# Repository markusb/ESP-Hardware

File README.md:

<H1>ESP-Hardware</H1>
<p>This repository contains my collection of ESP-Related hardware designs

<h2>ESP-8285 Miniboard</h2>

<p>Small DIL-size board for an ESP8285 Wifi microcontroller
<p>There already are a bunch of ESP boards and modules around, but the either add a full programming circuit or are modules with small pins to solder.
<p>This wants to combine the best of both, with standard 2.54mm pinheaders and easy programming, but on a separate board. So you plug in the programmer when you want to download firmware, but remove it when you don't need it anymore.
<ul>
<li>DIL size, plugs directly into a breadboard
<li>Breaks out all IO pins, not an arbitrary selection like most modules
<li>Antenna and crystal on board, ready to, just add power
<li>Optional red power and blue tx LED, to see whats going on, can be removed to save power
<li>No other, potentially unwanted hardware to get in the way of your design
</ul>

<h2>ESP82xx Programmer</H2>
<p>USB programmer built for the ESP-Miniboard, but it will work for normal ESP82xx circuits and most modules as well.
<p>As the ESP-Miniboard has no programmer, you need it separately. So it goes on this second board, to be removed when no longer in use.
<ul>
<li>USB-Serial chip (CH340)
<li>3.3V Regulator to feed the ESP from USB during programming (no external power needed)
<li>3.3V supply has a jumper to disable power and a polyfuse to protect from a short
<li>Nodemcu reset circuit to decouple the RTS/DTR lines from reset and GPIO0
<li>Works with any ESP module, just connect up the pins and off you go !
</ul>

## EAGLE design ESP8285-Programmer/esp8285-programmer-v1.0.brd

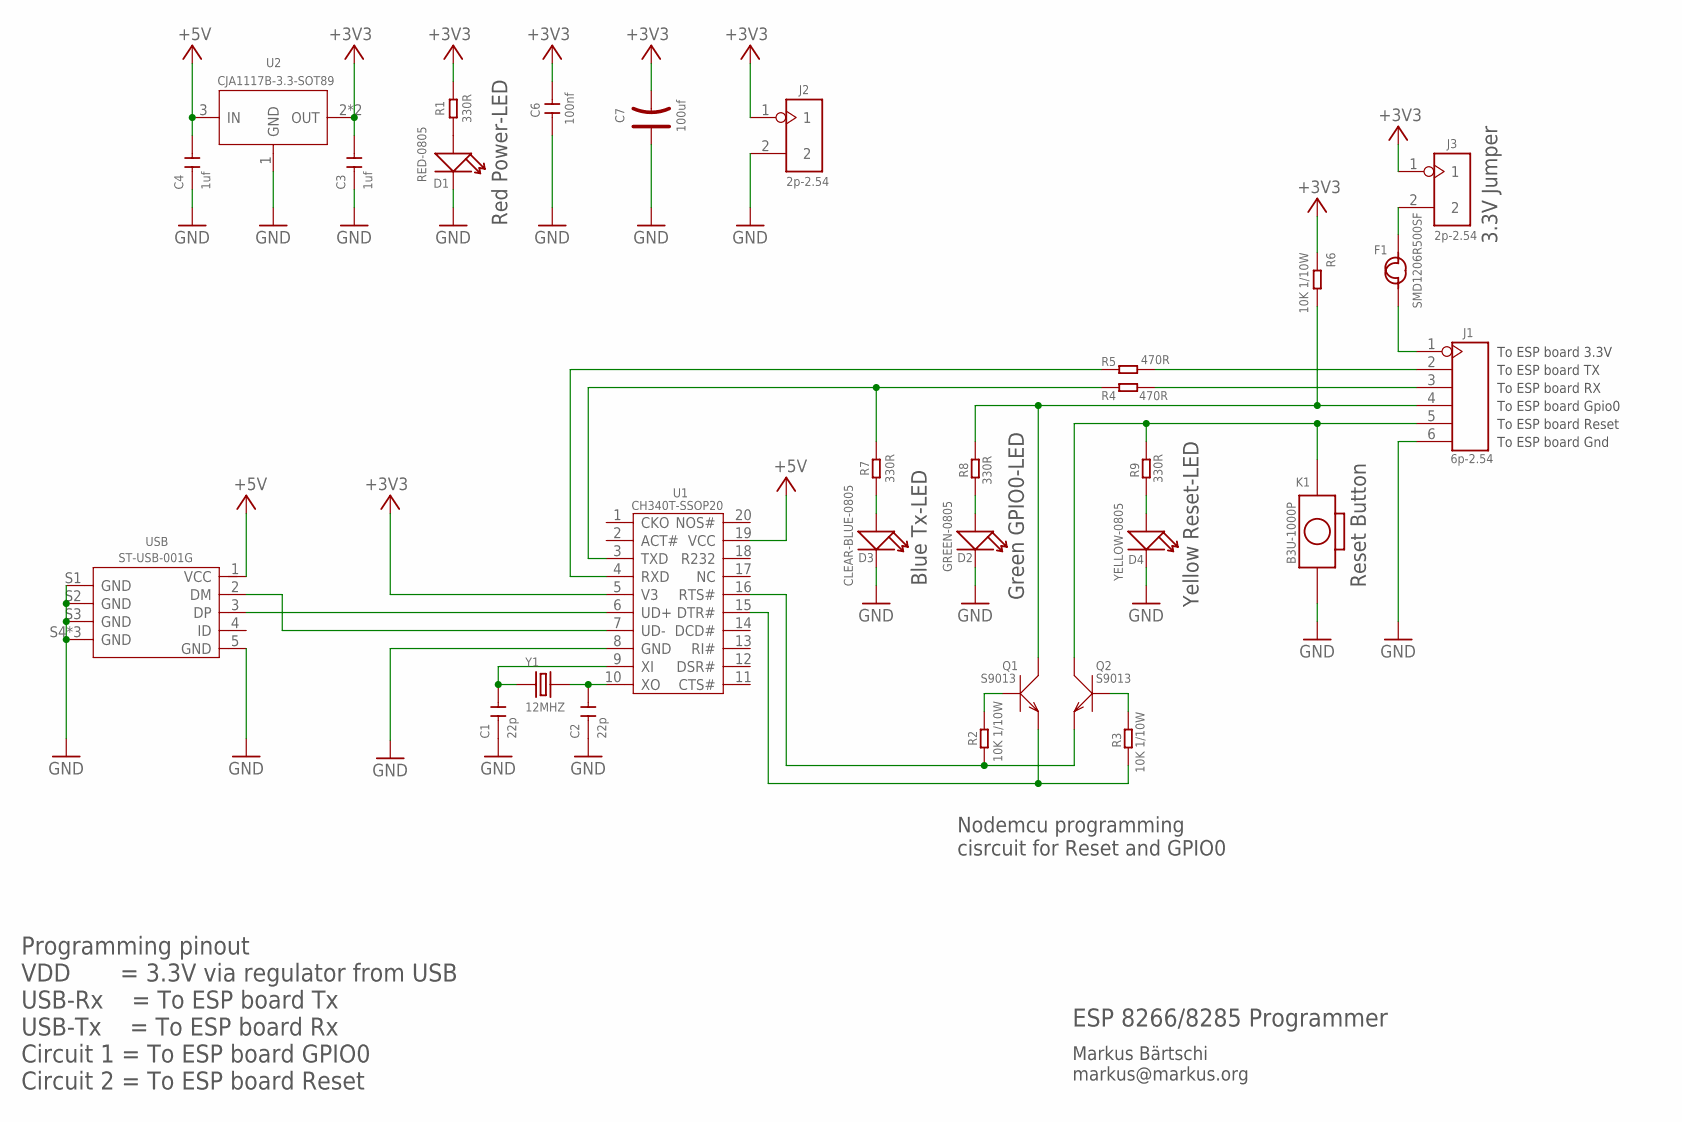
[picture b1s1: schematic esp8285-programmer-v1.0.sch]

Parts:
C1, C2: 22p; C0603
C3, C4: 1uf; C0603
C6: 100nf; C0603
C7: 100uf; AVX-B
D1: RED-0805; LED-0805
D2: GREEN-0805; LED-0805
D3: CLEAR-BLUE-0805; LED-0805
D4: YELLOW-0805; LED-0805
F1: SMD1206R500SF; F1206
J1: 6p-2.54; H6-2.54
J2, J3: 2p-2.54; H2-2.54
K1: B3U-1000P; SW2-SMD-3.0X2.5X1.2+0.4MM
Q1, Q2: S9013; SOT-23
R1, R7, R8, R9: 330R; R0603
R2, R3, R6: 10K 1/10W; R0603
R4, R5: 470R; R0603
U1: CH340T-SSOP20; SSOP20-0.65-7.6X5.2MM
U2: CJA1117B-3.3-SOT89; SOT-89
USB: ST-USB-001G; MICRO-USB5+4P-SMD-0.65-B
Y1: 12MHZ; X2-SMD-5.0X3.2X1.3MM

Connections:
+3V3: C3.2, C6.2, C7.-, J2.1, J3.1, R1.2, R6.1, U1.5 (V3), U2.2 (OUT), U2.4 (OUT)
+5V: C4.2, U1.19 (VCC), U2.3 (IN), USB.1 (VCC)
GND: C1.1, C2.1, C3.1, C4.1, C6.1, C7.+, D1.-, D2.-, D3.-, D4.-, J1.6, J2.2, K1.1, U1.8 (GND), U2.1 (GND), USB.5 (GND), USB.S1 (GND), USB.S2 (GND), USB.S3 (GND), USB.S4 (GND), USB.S5 (GND), USB.S6 (GND)
unnamed: F1.1, J1.1
unnamed: D1.+, R1.1
unnamed: F1.2, J3.2
unnamed: J1.2, R5.2
unnamed: C2.2, U1.10 (XO), Y1.2
unnamed: C1.2, U1.9 (XI), Y1.1
unnamed: J1.3, R4.2
unnamed: Q1.1 (B), R2.1
unnamed: Q2.1 (B), R3.1
unnamed: D3.+, R7.1
unnamed: D2.+, R8.1
unnamed: D4.+, R9.1
N$DTR: Q1.2 (E), R3.2, U1.15 (DTR#)
N$GPIO0: J1.4, Q1.3 (C), R6.2, R8.2
N$RESET: J1.5, K1.2, Q2.3 (C), R9.2
N$RTS: Q2.2 (E), R2.2, U1.16 (RTS#)
N$RX: R5.1, U1.4 (RXD)
N$TX: R4.1, R7.2, U1.3 (TXD)
N$USBD+: U1.6 (UD+), USB.3 (DP)
N$USBD-: U1.7 (UD-), USB.2 (DM)

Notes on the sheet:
Programming pinout VDD = 3.3V via regulator from USB USB-Rx = To ESP board Tx USB-Tx = To ESP board Rx Circuit 1 = To ESP board GPIO0 Circuit 2 = To ESP board Reset
To ESP board 3.3V
To ESP board TX
To ESP board RX
To ESP board Gpio0
To ESP board Reset
To ESP board Gnd
ESP 8266/8285 Programmer
Markus Bärtschi markus@markus.org
Nodemcu programming cisrcuit for Reset and GPIO0
Red Power-LED
Blue Tx-LED
Green GPIO0-LED
Yellow Reset-LED
Reset Button
3.3V Jumper

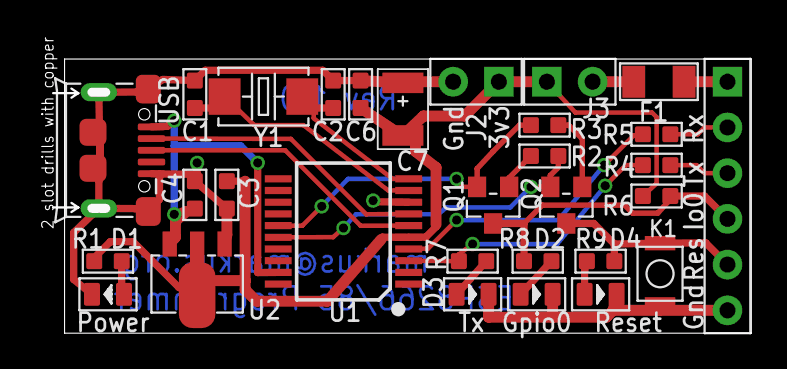
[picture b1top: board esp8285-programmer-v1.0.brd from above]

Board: 2 copper layers, 39.2 x 16.0 mm, 30 parts (0 on the bottom side), 23 nets.

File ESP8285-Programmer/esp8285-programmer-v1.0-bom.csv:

Part/Designator,Manufacture Part Number/Seeed SKU,Quantity,Description
"C1, C2",302010143,2,"302010143, 0603, 22pF"
"C3, C4",302010139,2,"302010139, 0603, 1uF"
"C6, C7",302010138,2,"302010138, 0603, 100nF"
D1,304090046,1,"304090046, LED, 0805, Red"
D2,304090057,1,"304090057, LED, 0805, Green"
D3,304090061,1,"304090061, LED, 0805, Blue"
D4,304090039,1,"304090039, LED, 0805, Yellow"
F1,307010002,1,"307010002, Fuse, 1206, 500mA"
K1,311020047,1,"311020047, Button"
"Q1, Q2",305010018,2,"305010018, Transistor, SOT23"
"R1, R7, R8, R9",301010300,4,"301010300, Res 330, 0603"
"R2, R3, R6",301010299,3,"301010299, Res 10k, 0603"
"R4, R5",301010088,2,"301010088, Res 470, 0603"
U1,310070026,1,"310070026, CH340T USB serial"
U2,310030095,1,"310030095, CJA1117B-3.3 Regulator"
USB,320010000,1,"320010000, USB Conn"
Y1,306010047,1,"306010047, 12Mhz Crystal"

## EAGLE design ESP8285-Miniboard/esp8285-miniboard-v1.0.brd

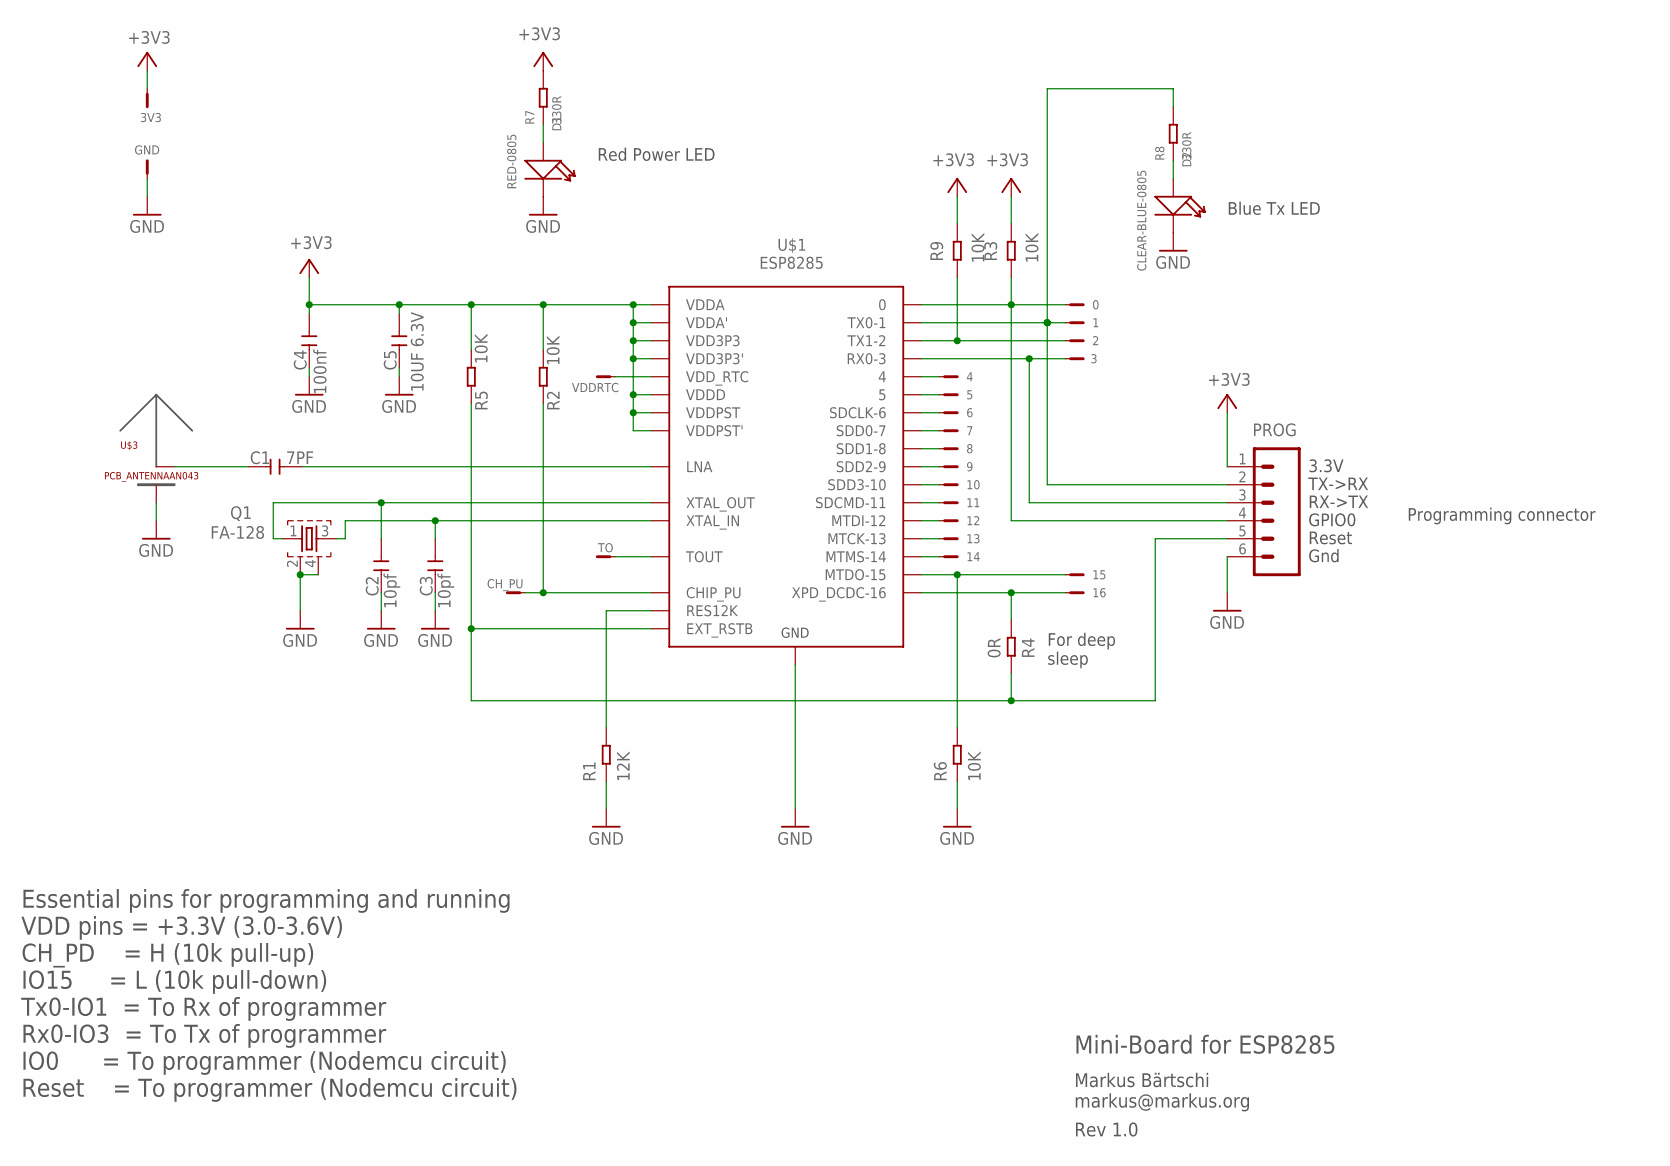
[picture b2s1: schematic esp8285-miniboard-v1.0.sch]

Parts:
0, 1, 2, 3, 3V3, 4, 5, 6, 7, 8, 9, 10, 11, 12, 13, 14, 15, 16: TESTPIN-1X1-SM; TESTPIN-HDR1X01
C1: 7PF; C0603
C2, C3: 10pf; C0603
C4: 100nf; C0603
C5: 10UF 6.3V; C0603
CH_PU: TESTPIN-1X1-SM; TESTPIN-HDR1X01
D1: RED-0805; LED-0805
D2: CLEAR-BLUE-0805; LED-0805
GND: TESTPIN-1X1-SM; TESTPIN-HDR1X01
PROG: M06SIP; 1X06
Q1: FA-128
R1: 12K; R0603
R2, R3, R5, R6, R9: 10K; R0603
R4: 0R; R0603
R7, R8: 330R; R0603
TO: TESTPIN-1X1-SM; TESTPIN-HDR1X01
U$1: ESP8285; QFN-32
U$3: PCB_ANTENNAAN043; PCB_ANTENNA_TI-AN043
VDDRTC: TESTPIN-1X1-SM; TESTPIN-HDR1X01

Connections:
+3V3: 3V3.1, C4.1, C5.1, PROG.1, R2.2, R3.2, R5.2, R7.2, R9.2, U$1.P$1 (VDDA), U$1.P$3 (VDD3P3), U$1.P$4 (VDD3P3'), U$1.P$11 (VDDPST), U$1.P$17 (VDDPST'), U$1.P$29 (VDDD), U$1.P$30 (VDDA')
GND: C2.1, C3.1, C4.2, C5.2, D1.-, D2.-, GND.1, PROG.6, Q1.2, Q1.4, R1.1, R6.1, U$1.33-GND (GND), U$3.GND
unnamed: D1.+, R7.1
unnamed: C1.1, U$3.ANT (AND)
unnamed: D2.+, R8.1
N$ANT: C1.2, U$1.P$2 (LNA)
N$CHIP_PU: CH_PU.1, R2.1, U$1.P$7 (CHIP_PU)
N$IO0: 0.1, PROG.4, R3.1, U$1.P$15 (0)
N$IO1: 1.1, PROG.2, R8.2, U$1.P$26 (TX0-1)
N$IO2: 2.1, R9.1, U$1.P$14 (TX1-2)
N$IO3: 3.1, PROG.3, U$1.P$25 (RX0-3)
N$IO4: 4.1, U$1.P$16 (4)
N$IO5: 5.1, U$1.P$24 (5)
N$IO6: 6.1, U$1.P$21 (SDCLK-6)
N$IO7: 7.1, U$1.P$22 (SDD0-7)
N$IO8: 8.1, U$1.P$23 (SDD1-8)
N$IO9: 9.1, U$1.P$18 (SDD2-9)
N$IO10: 10.1, U$1.P$19 (SDD3-10)
N$IO11: 11.1, U$1.P$20 (SDCMD-11)
N$IO12: 12.1, U$1.P$10 (MTDI-12)
N$IO13: 13.1, U$1.P$12 (MTCK-13)
N$IO14: 14.1, U$1.P$9 (MTMS-14)
N$IO15: 15.1, R6.2, U$1.P$13 (MTDO-15)
N$IO16: 16.1, R4.1, U$1.P$8 (XPD_DCDC-16)
N$RES12K: R1.2, U$1.P$31 (RES12K)
N$RESET: PROG.5, R4.2, R5.1, U$1.P$32 (EXT_RSTB)
N$TOUT: TO.1, U$1.P$6 (TOUT)
N$VDDRTC: U$1.P$5 (VDD_RTC), VDDRTC.1
N$XTAL-IN: C3.2, Q1.3, U$1.P$28 (XTAL_IN)
N$XTAL-OUT: C2.2, Q1.1, U$1.P$27 (XTAL_OUT)

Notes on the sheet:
Essential pins for programming and running VDD pins = +3.3V (3.0-3.6V) CH_PD = H (10k pull-up) IO15 = L (10k pull-down) Tx0-IO1 = To Rx of programmer Rx0-IO3 = To Tx of programmer IO0 = To programmer (Nodemcu circuit) Reset = To programmer (Nodemcu circuit)
3.3V
RX->TX
TX->RX
GPIO0
Reset
Gnd
Mini-Board for ESP8285
Rev 1.0
Markus Bärtschi markus@markus.org
Blue Tx LED
Red Power LED
For deep sleep
Programming connector

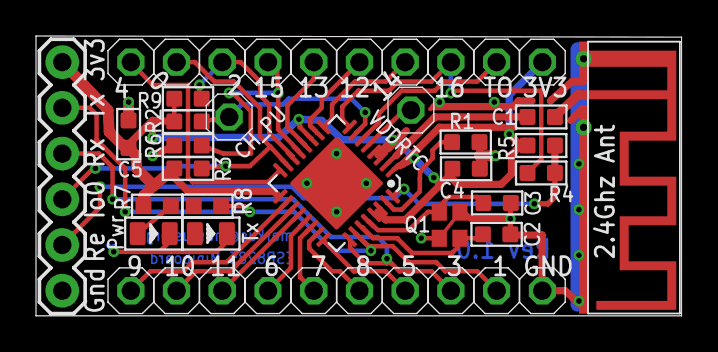
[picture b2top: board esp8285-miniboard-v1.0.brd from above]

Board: 2 copper layers, 35.9 x 15.5 mm, 42 parts (0 on the bottom side), 30 nets.

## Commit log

2016-07-17 added .gitignore
2016-07-17 Initial Rev 1
2016-07-17 gitignore
2016-07-17 added library
2016-07-17 Another Rev 1.0
2016-07-19 Hopefully final V1.0
2016-07-22 Final v1.0 fixed silkscreen, added testpoint, reduced via size
2016-07-24 Added BOM in Seeed format

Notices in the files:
parts and their libraries:
SparkFun: Licensing: CC v3.0 Share-Alike You are welcome to use this library for commercial purposes.
